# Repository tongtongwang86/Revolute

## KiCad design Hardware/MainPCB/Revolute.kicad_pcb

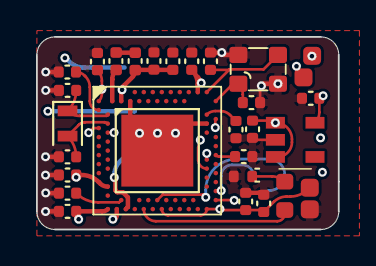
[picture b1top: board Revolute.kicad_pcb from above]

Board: 4 copper layers, 16.8 x 10.7 mm, 28 parts (0 on the bottom side), 23 nets.

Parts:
C1, C2, C17, C18: 12pF; C_0402_1005Metric
C5, C7, C8, C12: 100nF; C_0402_1005Metric
C6, C20, C21: 4.7uF; C_0402_1005Metric
C9: 820pF; C_0402_1005Metric
C10: 47nF; C_0402_1005Metric
C11: 100pF; C_0402_1005Metric
C13, C14, C15, C16: 1uF; C_0402_1005Metric
D1: BLUE; LED_0603_1608Metric-nosilk
J1: USB_A; USB_Intergrated
L2: 10uH; L_0402_1005Metric
L3: 15nH; L_0402_1005Metric
R1: 1.5k; Resistor_0402_1005M-nosilk
U1: nRF52840_aQFN73; AQFN-73-1EP_7x7mm_P0.5mm_NRF52840-custom
U3: AP2112K-3.3; SOT-23-5
U4: debug_ports; Debug pin cluster
X1: 32MHZ; crystal 32mhz
X2: 32.768 kHz; Crystal_SMD_2012-2Pin_2.0x1.2mm

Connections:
BLUE_LED: D1.2 (A), U1.AD10 (P0.15)
GND: C1.1, C2.1, C5.2, C6.1, C7.1, C8.1, C9.1, C10.2, C11.1, C12.2, C13.2, C14.2, C15.2, C16.2, C17.2, C18.2, C20.1, C21.2, J1.4 (GND), R1.1, U1.B7 (VSS), U1.EP (VSS), U1.F23 (VSS_PA), U3.2 (GND), U4.1 (GND), U4.8 (GND), X1.2, X1.4
unnamed: D1.1 (K), R1.2
unnamed: J1.3 (D+), U1.AD6 (D+)
unnamed: J1.2 (D-), U1.AD4 (D-)
unnamed: L2.1, L3.2
unnamed: L2.2, U1.B3 (DCC)
unnamed: C5.1, U1.C1 (DEC1)
unnamed: C11.2, U1.D23 (DEC3)
unnamed: C10.1, C15.1, L3.1, U1.B5 (DEC4), U1.E24 (DEC6)
unnamed: C9.2, U1.N24 (DEC5)
unnamed: C20.2, U1.AC5 (DECUSB)
unnamed: U1.AC13 (P0.18/~RESET), U4.7 (reset)
unnamed: C1.2, U1.B24 (XC1), X1.1
unnamed: C2.2, U1.A23 (XC2), X1.3
unnamed: C17.1, U1.D2 (XL1/P0.00), X2.1
unnamed: C18.1, U1.F2 (XL2/P0.01), X2.2
P0.26: U1.G1 (P0.26), U4.2 (SDA)
P0.27: U1.H2 (P0.27), U4.3 (SCL)
VBUS: C13.1, C21.1, J1.1 (VBUS), U1.AD2 (VBUS), U3.1 (VIN), U3.3 (EN)
VDD_nRF: C6.2, C7.2, C8.2, C12.1, C14.1, C16.1, U1.A22 (VDD), U1.AD14 (VDD), U1.AD23 (VDD), U1.B1 (VDD), U1.W1 (VDD), U1.Y2 (VDDH), U3.5 (VOUT), U4.4 (VDD)
swc: U1.AA24 (SWDCLK), U4.6 (swc)
swd: U1.AC24 (SWDIO), U4.5 (swd)

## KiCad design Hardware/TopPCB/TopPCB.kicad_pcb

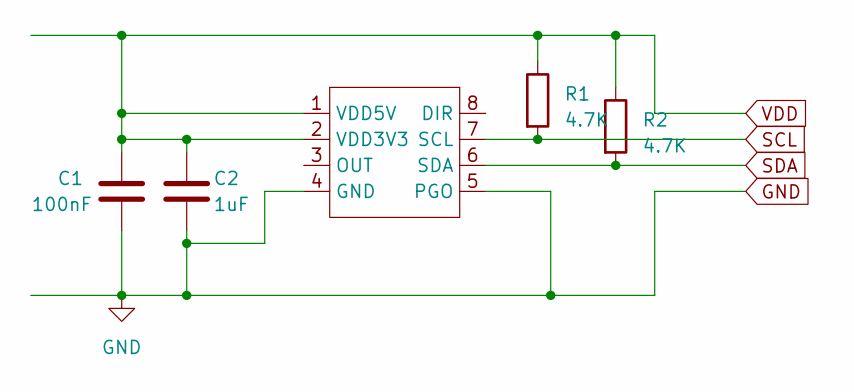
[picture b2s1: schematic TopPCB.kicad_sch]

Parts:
C1: 100nF; C_0402_1005Metric
C2: 1uF; C_0402_1005Metric
R1, R2: 4.7K; R_0402_1005Metric
U1: SOIC-8-1EP_3.9x4.9mm_P1.27mm_EP2.514x3.2mm

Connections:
GND: C1.2, C2.2, U1.4 (GND), U1.5 (PGO)
SCL: R1.2, U1.7 (SCL)
SDA: R2.2, U1.6 (SDA)
VDD: C1.1, C2.1, R1.1, R2.1, U1.1 (VDD5V), U1.2 (VDD3V3)

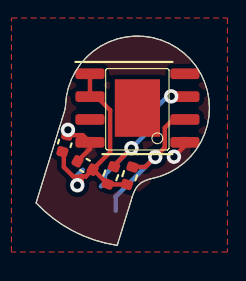
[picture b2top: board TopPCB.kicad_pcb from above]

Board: 4 copper layers, 9.6 x 11.6 mm, 5 parts (0 on the bottom side), 4 nets.
